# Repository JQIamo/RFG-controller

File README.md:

# RFG-Controller

Flow interlock and remote controller for RFG-380k for Er induction oven. Interfaces with a DAQ (e.g. NI USB-6002) to ramp oven temperature.

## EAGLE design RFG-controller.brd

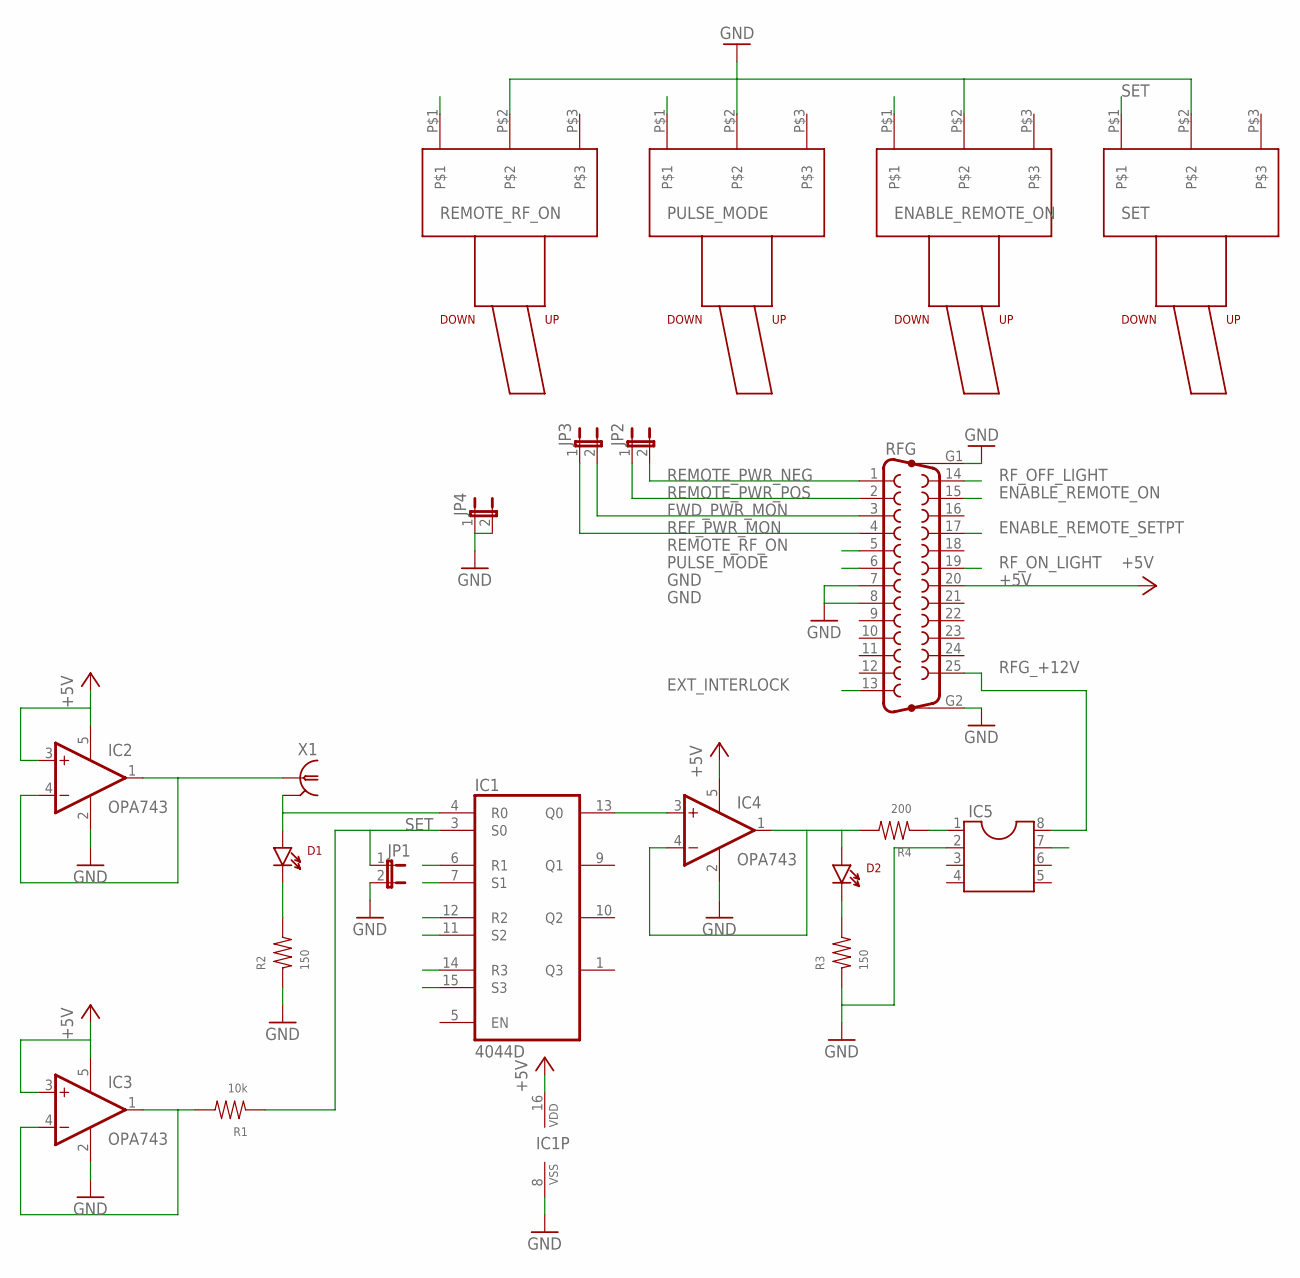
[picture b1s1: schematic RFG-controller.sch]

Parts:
D1, D2: LED; LTL-533-11
ENABLE_REMOTE_ON: SPDT-TOGGLE; 7101MD9AV2BE
IC1: 4044D; SO16
IC2, IC3, IC4: OPA743; SOT23-5
IC5: DIL8; DIL08
JP1, JP2, JP3, JP4: JP1E; JP1
PULSE_MODE: SPDT-TOGGLE; 7101MD9AV2BE
R1: 10k; 0603
R2, R3: 150; 0603
R4: 200; 0603
REMOTE_ON: SPDT-TOGGLE; 7101MD9AV2BE
RFG: F25HP
SET: SPDT-TOGGLE; 7101MD9AV2BE
X1: BNC-H; BNC90

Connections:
+5V: IC1.16 (VDD), IC2.3 (+IN), IC2.5 (V+), IC3.3 (+IN), IC3.5 (V+), IC4.5 (V+), RFG.20
ENABLE_REMOTE_ON: ENABLE_REMOTE_ON.P$1, RFG.15
ENABLE_REMOTE_SETPT: RFG.17
EXT_INTERLOCK: IC5.7, RFG.13
FWD_PWR_MON: JP3.2, RFG.3
GND: ENABLE_REMOTE_ON.P$2, IC1.6 (R1), IC1.7 (S1), IC1.8 (VSS), IC1.11 (S2), IC1.12 (R2), IC1.14 (R3), IC1.15 (S3), IC2.2 (V-), IC3.2 (V-), IC4.2 (V-), IC5.2, JP1.2, JP4.1, JP4.2, PULSE_MODE.P$2, R2.1, R3.1, REMOTE_ON.P$2, RFG.7, RFG.8, RFG.G1, RFG.G2, SET.P$2
unnamed: IC2.1 (OUT), IC2.4 (-IN), X1.1
unnamed: IC3.1 (OUT), IC3.4 (-IN), R1.2
unnamed: IC5.1, R4.1
unnamed: D2.A, IC4.1 (OUT), IC4.4 (-IN), R4.2
unnamed: IC1.13 (Q0), IC4.3 (+IN)
unnamed: D1.A, IC1.4 (R0), X1.2
unnamed: D1.C, R2.2
unnamed: D2.C, R3.2
PULSE_MODE: PULSE_MODE.P$1, RFG.6
REF_PWR_MON: JP3.1, RFG.4
REMOTE_PWR_NEG: JP2.2, RFG.1
REMOTE_PWR_POS: JP2.1, RFG.2
REMOTE_RF_ON: REMOTE_ON.P$1, RFG.5
RFG_+12V: IC5.8, RFG.25
RF_OFF_LIGHT: RFG.14
RF_ON_LIGHT: RFG.19
SET: IC1.3 (S0), JP1.1, R1.1, SET.P$1

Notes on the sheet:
SET

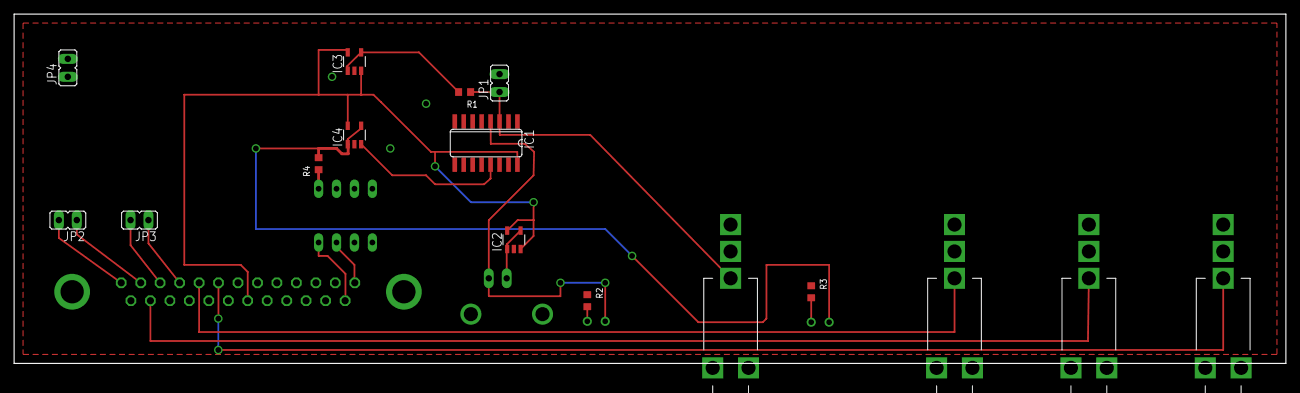
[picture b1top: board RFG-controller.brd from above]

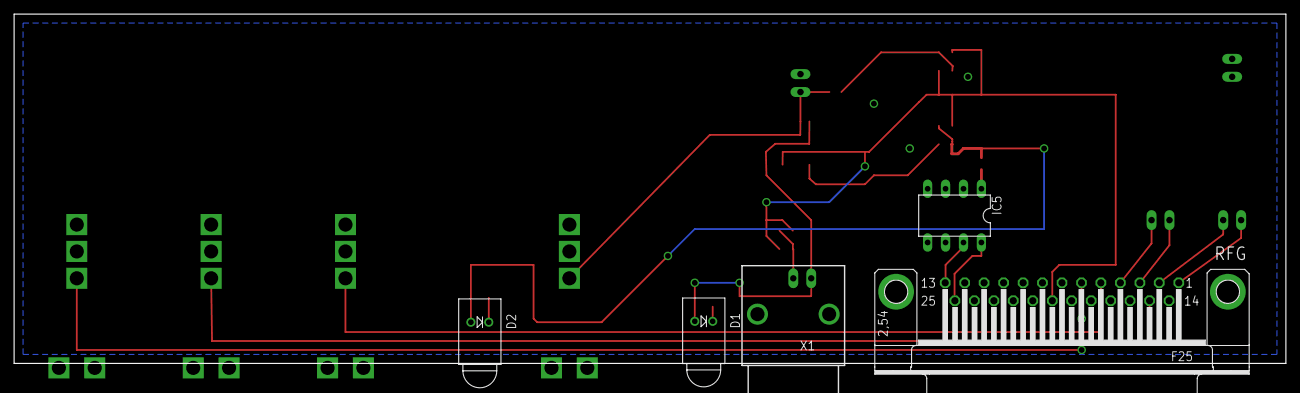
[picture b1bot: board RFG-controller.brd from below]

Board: 2 copper layers, 180.3 x 49.5 mm, 21 parts (5 on the bottom side), 20 nets.

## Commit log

2019-06-27 added README
